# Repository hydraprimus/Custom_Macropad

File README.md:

This is the locked in hackpad, my first hardware design. It is a 3x3 macropad, with a rotary encoder for volume and a 0.91 in OLED. 

The 9 buttons perform these functions: power off, system sleep, system wake, rewidn media, pause/play media, fast forward media, copy, paste, and find.

The hackpad case is decorated with a big LOCK IN text to remind the user (me) to stop scrolling and lock in. 

The non-plastic elements in the .step file were taken from GrabCad from these creators:
DSA keycap: zim cad
Cherry MX red switch: Baco
Seeed Studio XIAO rp2040: Seeed Studio
EC11 rotary encoder: Xindela
0.91" OLED display: John England

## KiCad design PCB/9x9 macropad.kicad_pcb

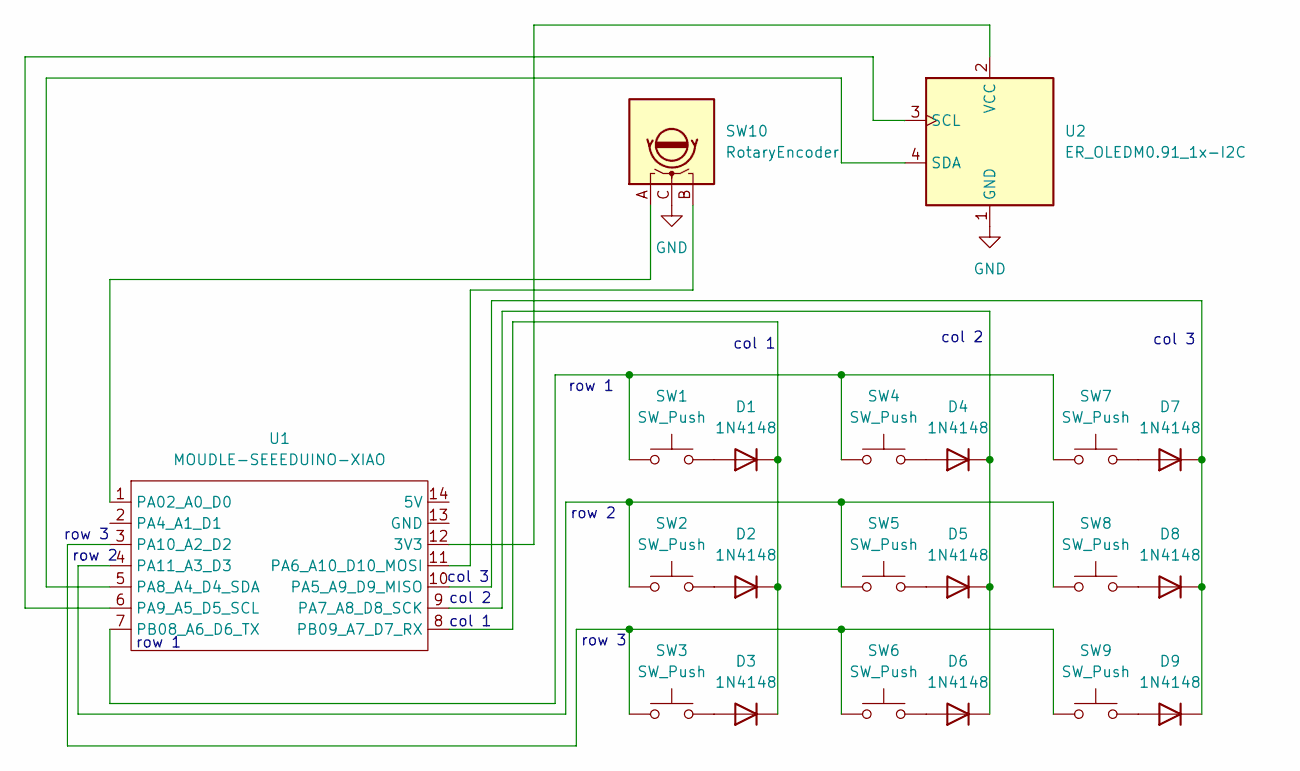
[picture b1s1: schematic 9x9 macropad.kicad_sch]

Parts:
D1, D2, D3, D4, D5, D6, D7, D8, D9: 1N4148; D_DO-35_SOD27_P7.62mm_Horizontal
SW1, SW2, SW3, SW4, SW5, SW6, SW7, SW8, SW9: SW_Push; SW_Cherry_MX_1.00u_PCB
SW10: RotaryEncoder; RotaryEncoder_Alps_EC11E-Switch_Vertical_H20mm
U1: MOUDLE-SEEEDUINO-XIAO; XIAO-Generic-Hybrid-14P-2.54-21X17.8MM
U2: ER_OLEDM0.91_1x-I2C

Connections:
GND: SW10.C, U2.1 (GND)
unnamed: D1.2 (A), SW1.2
unnamed: D1.1 (K), D2.1 (K), D3.1 (K), U1.8 (PB09_A7_D7_RX)
unnamed: D2.2 (A), SW2.2
unnamed: D3.2 (A), SW3.2
unnamed: D4.2 (A), SW4.2
unnamed: D4.1 (K), D5.1 (K), D6.1 (K), U1.9 (PA7_A8_D8_SCK)
unnamed: D5.2 (A), SW5.2
unnamed: D6.2 (A), SW6.2
unnamed: D7.2 (A), SW7.2
unnamed: D7.1 (K), D8.1 (K), D9.1 (K), U1.10 (PA5_A9_D9_MISO)
unnamed: D8.2 (A), SW8.2
unnamed: D9.2 (A), SW9.2
unnamed: U1.12 (3V3), U2.2 (VCC)
unnamed: SW10.A, U1.1 (PA02_A0_D0)
unnamed: SW10.B, U1.11 (PA6_A10_D10_MOSI)
unnamed: U1.5 (PA8_A4_D4_SDA), U2.4 (SDA)
unnamed: U1.6 (PA9_A5_D5_SCL), U2.3 (SCL)
unnamed: SW3.1, SW6.1, SW9.1, U1.3 (PA10_A2_D2)
unnamed: SW2.1, SW5.1, SW8.1, U1.4 (PA11_A3_D3)
unnamed: SW1.1, SW4.1, SW7.1, U1.7 (PB08_A6_D6_TX)

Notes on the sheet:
col 3
row 1
col 1
row 2
row 3
col 2

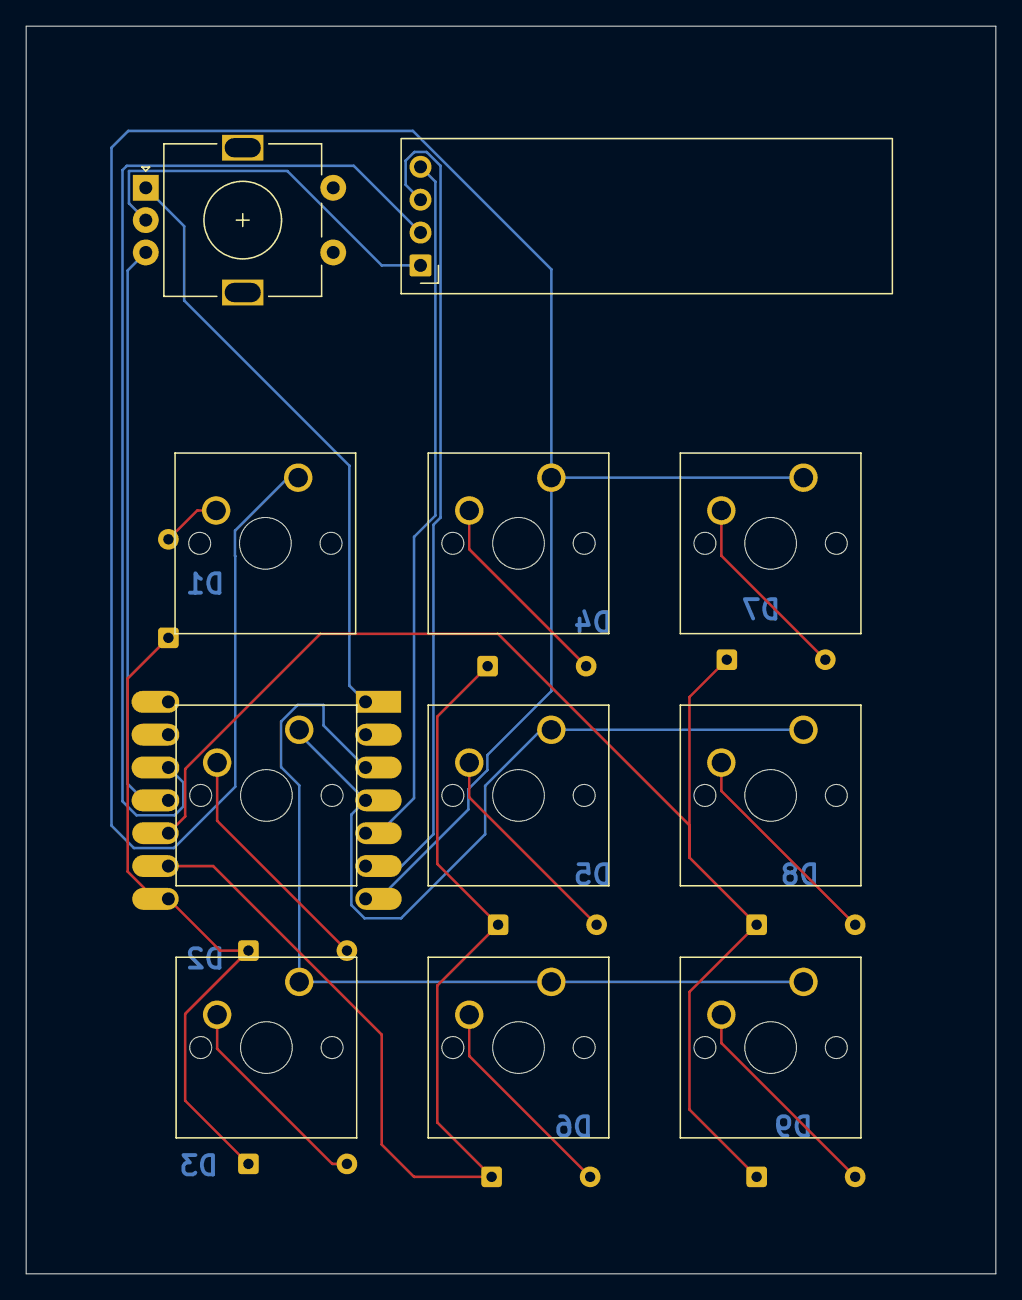
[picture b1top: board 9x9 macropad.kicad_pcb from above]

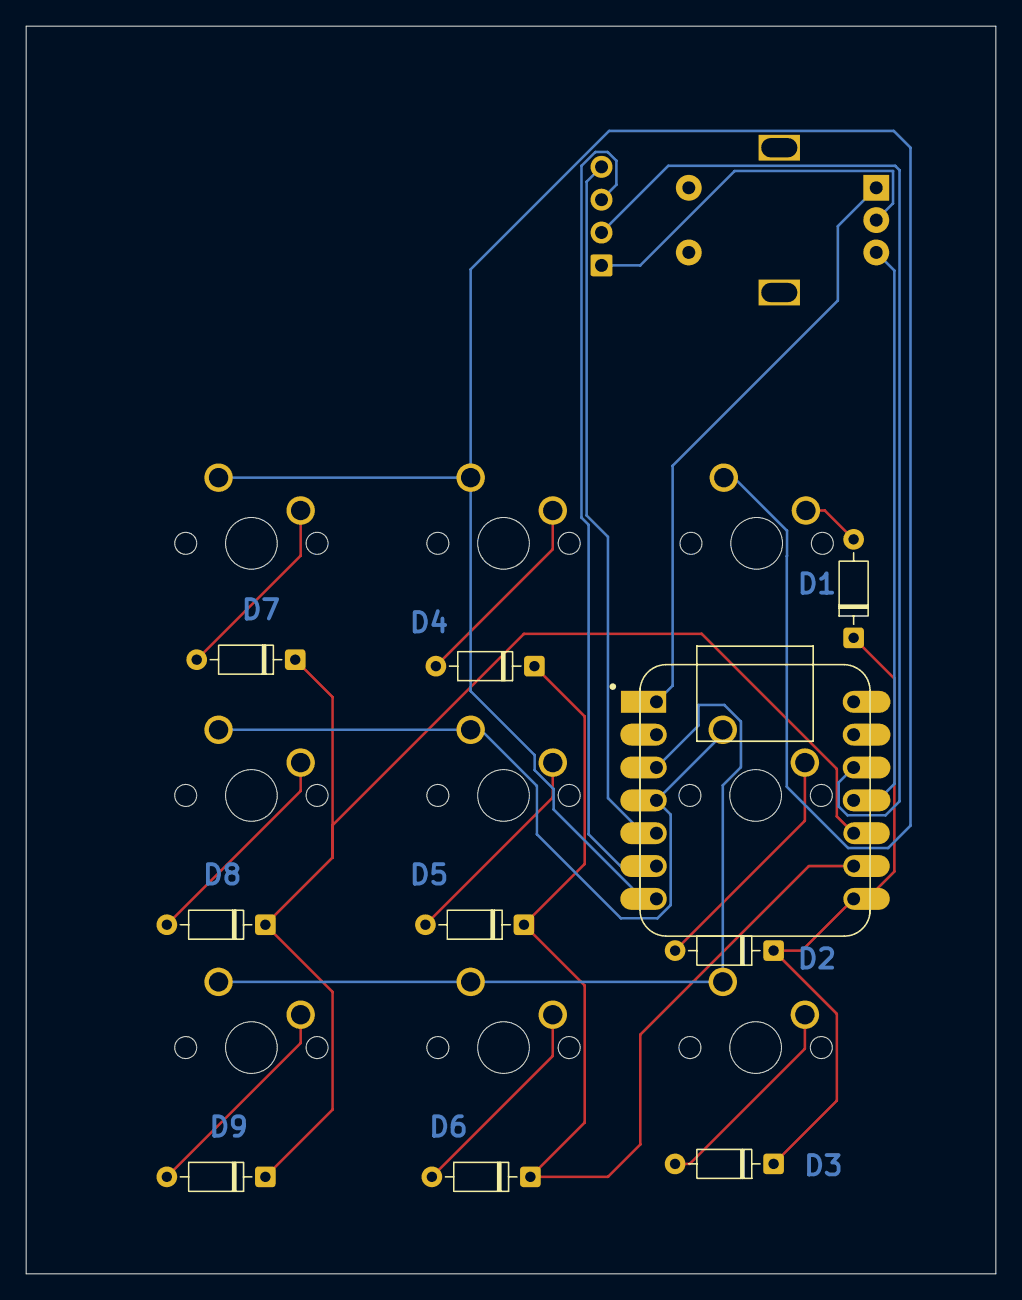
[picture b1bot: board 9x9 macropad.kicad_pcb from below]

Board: 2 copper layers, 75.0 x 96.5 mm, 21 parts (10 on the bottom side), 21 nets.
